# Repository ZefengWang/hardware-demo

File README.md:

# hardware-demo

## Preview
### Front

### Back

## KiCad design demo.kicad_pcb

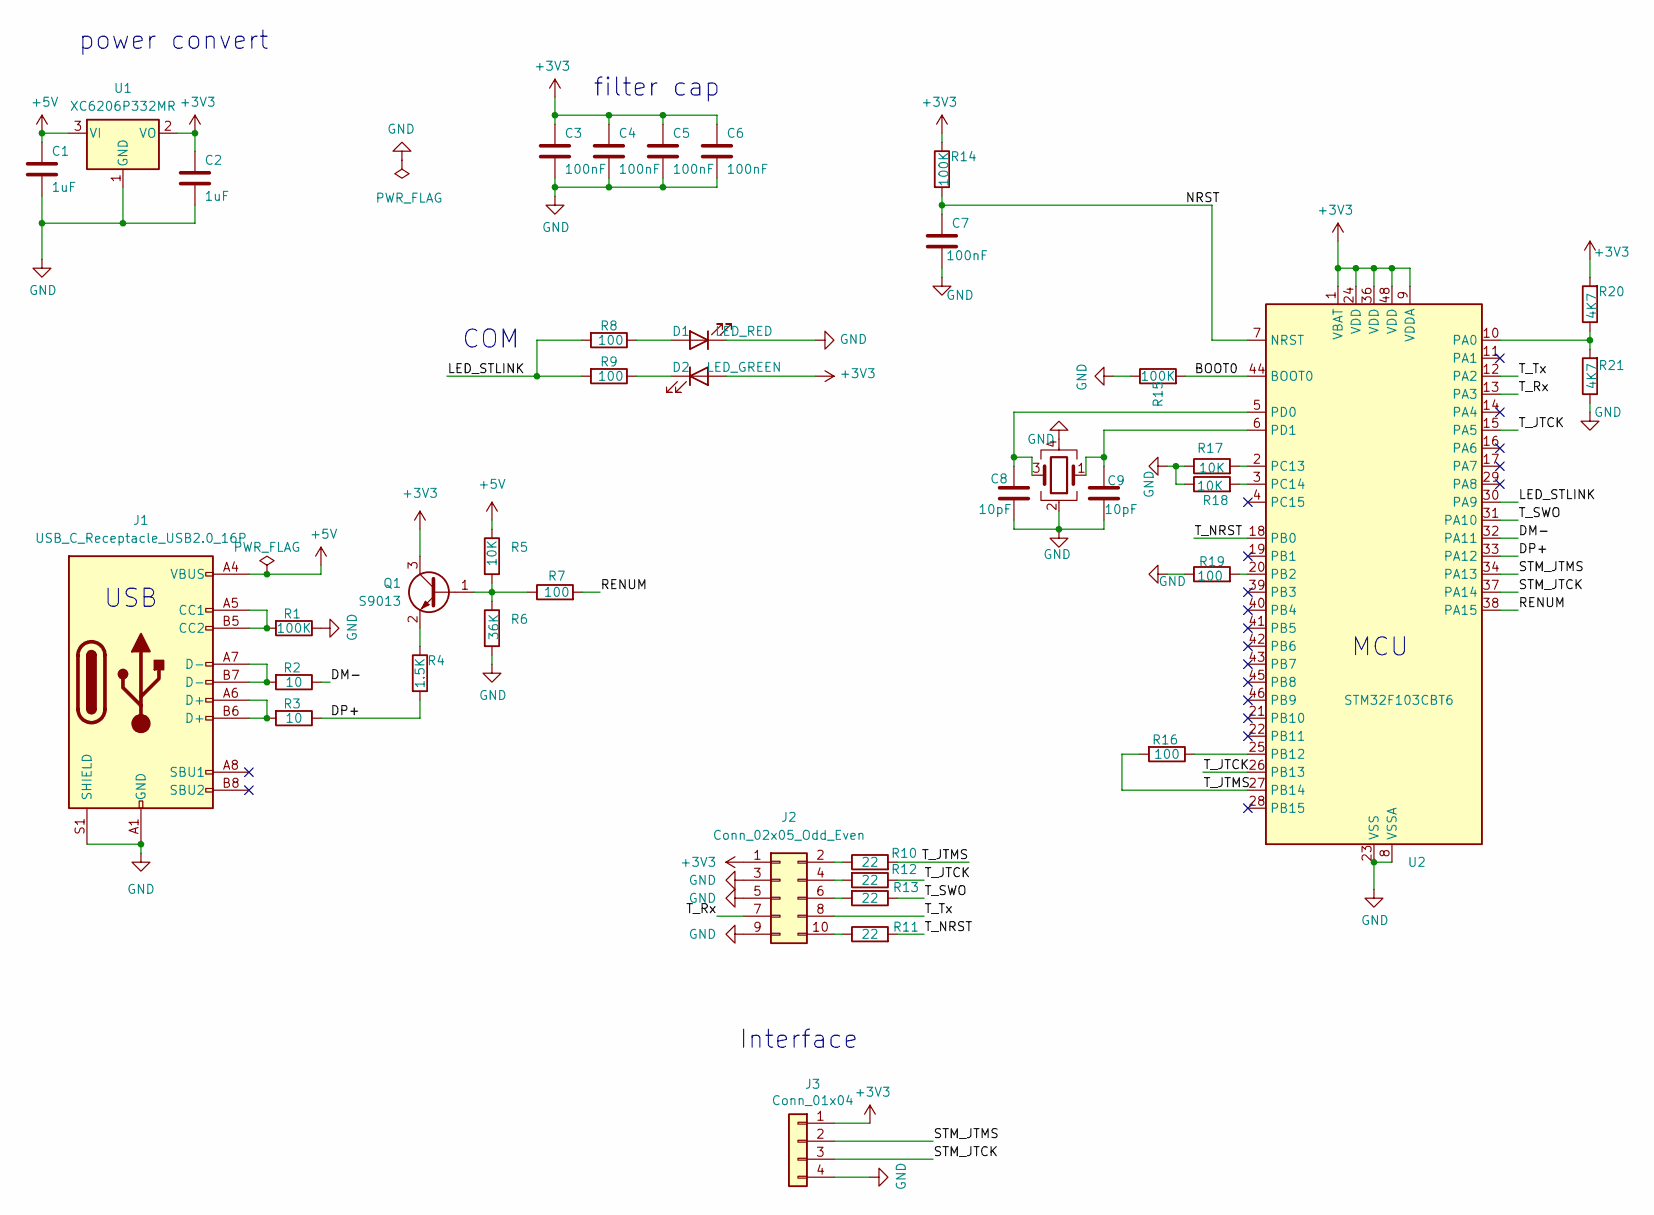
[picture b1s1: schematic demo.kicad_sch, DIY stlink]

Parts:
C1, C2: 1uF; C_0402_1005Metric
C3, C4, C5, C6, C7: 100nF; C_0402_1005Metric
C8, C9: 10pF; C_0402_1005Metric
D1: LED_RED; LED_0402_1005Metric
D2: LED_GREEN; LED_0402_1005Metric
J1: USB_C_Receptacle_USB2.0_16P; USB_C_Receptacle_GCT_USB4105-xx-A_16P_TopMnt_Horizontal
J2: Conn_02x05_Odd_Even; pin-header-hor-handsolid-2x5
J3: Conn_01x04; PinHeader_1x04_P1.27mm_Vertical
Q1: S9013; SOT-23
R1, R14, R15: 100K; R_0402_1005Metric
R2, R3: 10; R_0402_1005Metric
R4: 1.5K; R_0402_1005Metric
R5, R17, R18: 10K; R_0402_1005Metric
R6: 36K; R_0402_1005Metric
R7, R8, R9, R16, R19: 100; R_0402_1005Metric
R10, R11, R12, R13: 22; R_0402_1005Metric
R20, R21: 4K7; R_0402_1005Metric
U1: XC6206P332MR; SOT-23-3
U2: STM32F103CBT6; LQFP-48_7x7mm_P0.5mm
Y1: 8M; Crystal_SMD_3225-4Pin_3.2x2.5mm

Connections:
+3V3: C2.1, C3.1, C4.1, C5.1, C6.1, D2.2 (A), J2.1, J3.1, Q1.3 (C), R14.1, R20.2, U1.2 (VO), U2.1 (VBAT), U2.9 (VDDA), U2.24 (VDD), U2.36 (VDD), U2.48 (VDD)
+5V: C1.1, J1.A4 (VBUS), J1.A9 (VBUS), J1.B4 (VBUS), J1.B9 (VBUS), R5.1, U1.3 (VI)
/BOOT0: R15.2, U2.44 (BOOT0)
/DM-: R2.1, U2.32 (PA11)
/DP+: R3.1, R4.2, U2.33 (PA12)
/LED_STLINK: R8.2, R9.2, U2.30 (PA9)
/NRST: C7.1, R14.2, U2.7 (NRST)
/RENUM: R7.2, U2.38 (PA15)
/STM_JTCK: J3.3, U2.37 (PA14)
/STM_JTMS: J3.2, U2.34 (PA13)
/T_JTCK: R12.1, U2.15 (PA5), U2.26 (PB13)
/T_JTMS: R10.2, R16.2, U2.27 (PB14)
/T_NRST: R11.2, U2.18 (PB0)
/T_Rx: J2.7, U2.13 (PA3)
/T_SWO: R13.1, U2.31 (PA10)
/T_Tx: J2.8, U2.12 (PA2)
GND: C1.2, C2.2, C3.2, C4.2, C5.2, C6.2, C7.2, C8.1, C9.1, D1.1 (K), J1.A1 (GND), J1.A12 (GND), J1.B1 (GND), J1.B12 (GND), J1.S1 (SHIELD), J2.3, J2.5, J2.9, J3.4, R1.1, R6.2, R15.1, R17.1, R18.1, R19.1, R21.1, U1.1 (GND), U2.8 (VSSA), U2.23 (VSS), U2.35 (VSS), U2.47 (VSS), Y1.2, Y1.4
unnamed: D1.2 (A), R8.1
unnamed: D2.1 (K), R9.1
unnamed: J1.A5 (CC1), J1.B5 (CC2), R1.2
unnamed: J1.A6 (D+), J1.B6 (D+), R3.2
unnamed: J1.A7 (D-), J1.B7 (D-), R2.2
unnamed: J2.2, R10.1
unnamed: J2.4, R12.2
unnamed: J2.6, R13.2
unnamed: J2.10, R11.1
unnamed: Q1.1 (B), R5.2, R6.1, R7.1
unnamed: Q1.2 (E), R4.1
unnamed: R20.1, R21.2, U2.10 (PA0)
unnamed: R19.2, U2.20 (PB2)
unnamed: R16.1, U2.25 (PB12)
unnamed: R17.2, U2.2 (PC13)
unnamed: R18.2, U2.3 (PC14)
unnamed: C8.2, U2.5 (PD0), Y1.3
unnamed: C9.2, U2.6 (PD1), Y1.1

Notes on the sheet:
MCU
Interface
USB
filter cap
power convert
COM

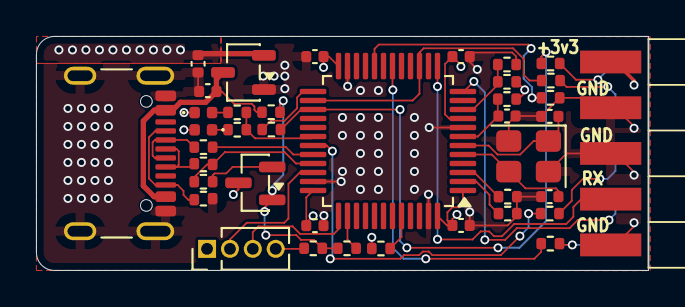
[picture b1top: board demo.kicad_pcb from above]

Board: 4 copper layers, 34.0 x 13.0 mm, 39 parts (0 on the bottom side), 35 nets.

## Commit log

2021-10-25 push test
2021-10-25 Revert "push test"
    This reverts commit 291c0c4fd816dd9c8f64d37a9b3e81b216759de6.
2022-01-09 update pcb and sch
2022-01-17 v1.0.0
2022-01-17 add readme preview
2022-01-19 Create LICENSE
2023-03-11 add usb typec-2.0 fp
2023-03-12 update files
2023-03-12 update jpg
2023-03-13 update to product
2025-11-19 update sch
2025-11-23 V1.0.2
2025-11-25 modify hole size at min 0.3mm
2025-12-13 1.3*3.8(cm^2) relayout
2025-12-13 V1.0.3
2025-12-13 V1.0.4
2025-12-13 V1.0.4 gerber
